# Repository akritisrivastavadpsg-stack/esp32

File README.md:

# esp32 Introduction

##
A basic ESP32 hardware project designed using KiCad. This repository contains the schematic and PCB layout files for an ESP32-based setup, intended for learning, experimentation, and future expansion.

📌 Project Overview

This project focuses on:

Understanding ESP32 pin mapping

Creating a clean schematic

Designing a basic PCB layout in KiCad

Laying groundwork for firmware-based ESP32 projects

No unnecessary complexity. Just the essentials done right.

🛠 Tools & Software

KiCad (v6 or later recommended)

ESP32 module (e.g., ESP32-WROOM-32)

Basic understanding of schematics & PCB design

/kicad/ 
├── schematic.sch 
├── pcb_layout.kicad_pcb 
└── project.kicad_pro

🔌 Hardware Features

ESP32 microcontroller

Power input section

Basic pin breakout for GPIO access

Designed for easy modification and upgrades

🚀 How to Use

Clone the repository:

git clone https://github.com/akritisrivastava20/esp32.git

Open the project in KiCad

Review the schematic

Inspect or modify the PCB layout

Export Gerber files if you plan to manufacture

⚠️ Notes

This is a basic-level project

Not optimized for production use

Always double-check power and pin connections before fabrication

📈 Future Improvements

Add USB-to-UART circuit

Voltage regulation improvements

On-board sensors or peripherals

Firmware examples (Arduino / ESP-IDF)

📜 License

This project is open-source. Use it, modify it, break it, learn from it.

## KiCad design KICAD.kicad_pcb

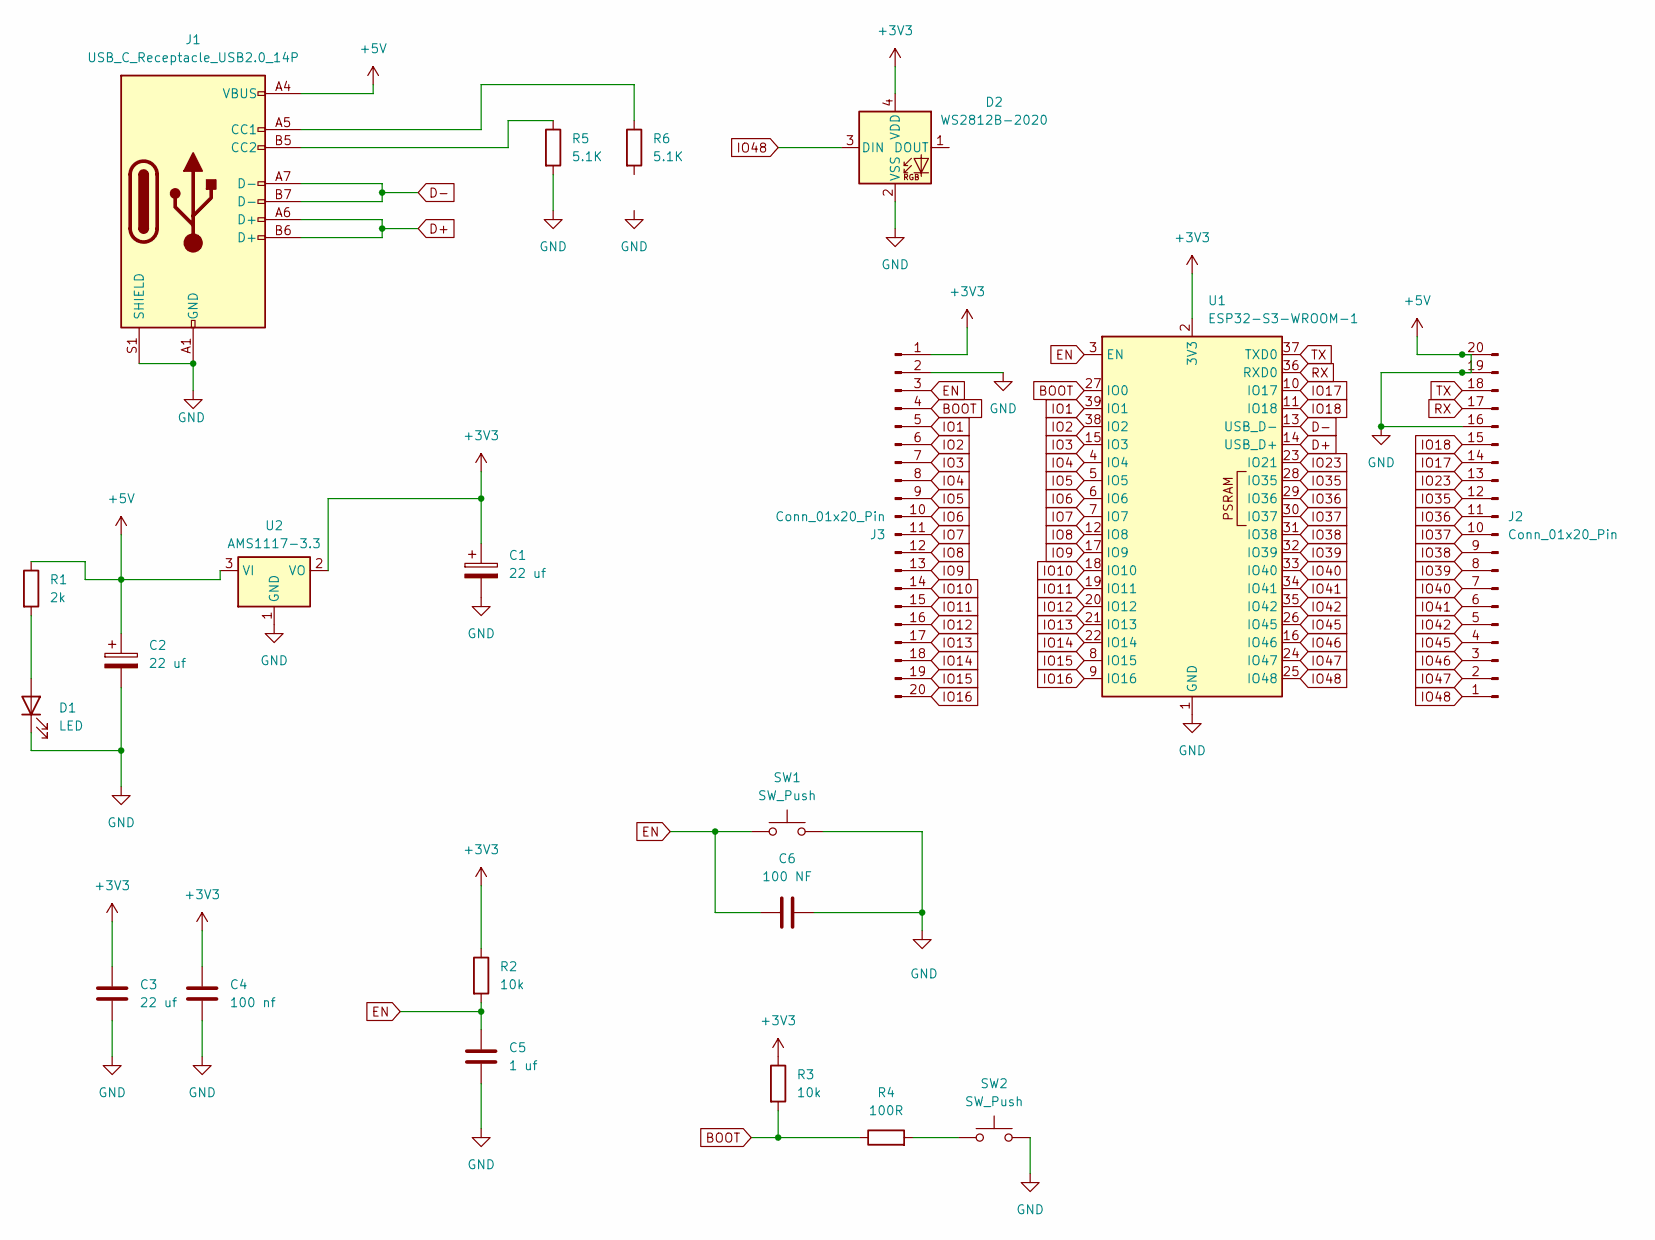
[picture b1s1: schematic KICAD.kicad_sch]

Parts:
C1, C2: 22 uf; CP_EIA-3528-12_Kemet-T
C3: 22 uf; C_0805_2012Metric
C4: 100 nf; C_0805_2012Metric
C5: 1 uf; C_0805_2012Metric
C6: 100 NF; C_0805_2012Metric
D1: LED; LED_0805_2012Metric
D2: WS2812B-2020; LED_WS2812B-2020_PLCC4_2.0x2.0mm
J1: USB_C_Receptacle_USB2.0_14P; USB_C_Receptacle_GCT_USB4105-xx-A_16P_TopMnt_Horizontal
J2, J3: Conn_01x20_Pin; PinHeader_1x20_P2.54mm_Vertical
R1: 2k; R_0805_2012Metric
R2, R3: 10k; R_0805_2012Metric
R4: 100R; R_0805_2012Metric
R5, R6: 5.1K; R_0805_2012Metric
SW1, SW2: SW_Push; SW_Push_SPST_NO_Alps_SKRK
U1: ESP32-S3-WROOM-1
U2: AMS1117-3.3; SOT-223-3_TabPin2

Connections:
+3V3: C1.1, C3.1, C4.1, D2.4 (VDD), J3.1, R2.1, R3.1, U1.2 (3V3), U2.2 (VO)
+5V: C1.2, C2.1, C2.2, C3.2, C4.2, C5.2, C6.2, D1.1 (K), D2.2 (VSS), J1.A1 (GND), J1.A4 (VBUS), J1.A9 (VBUS), J1.A12 (GND), J1.B1 (GND), J1.B4 (VBUS), J1.B9 (VBUS), J1.B12 (GND), J1.S1 (SHIELD), J2.16, J2.19, J2.20, J3.2, R1.1, R5.2, SW1.2, SW2.2, U1.1 (GND), U1.40 (GND), U1.41 (GND), U2.1 (GND), U2.3 (VI)
BOOT: J3.4, R3.2, R4.1, U1.27 (IO0)
D+: J1.A6 (D+), J1.B6 (D+), U1.14 (USB_D+)
D-: J1.A7 (D-), J1.B7 (D-), U1.13 (USB_D-)
EN: C5.1, C6.1, J3.3, R2.2, SW1.1, U1.3 (EN)
IO1: J3.5, U1.39 (IO1)
IO2: J3.6, U1.38 (IO2)
IO3: J3.7, U1.15 (IO3)
IO4: J3.8, U1.4 (IO4)
IO5: J3.9, U1.5 (IO5)
IO6: J3.10, U1.6 (IO6)
IO7: J3.11, U1.7 (IO7)
IO8: J3.12, U1.12 (IO8)
IO9: J3.13, U1.17 (IO9)
IO10: J3.14, U1.18 (IO10)
IO11: J3.15, U1.19 (IO11)
IO12: J3.16, U1.20 (IO12)
IO13: J3.17, U1.21 (IO13)
IO14: J3.18, U1.22 (IO14)
IO15: J3.19, U1.8 (IO15)
IO16: J3.20, U1.9 (IO16)
IO17: J2.14, U1.10 (IO17)
IO18: J2.15, U1.11 (IO18)
IO23: J2.13, U1.23 (IO21)
IO35: J2.12, U1.28 (IO35)
IO36: J2.11, U1.29 (IO36)
IO37: J2.10, U1.30 (IO37)
IO38: J2.9, U1.31 (IO38)
IO39: J2.8, U1.32 (IO39)
IO40: J2.7, U1.33 (IO40)
IO41: J2.6, U1.34 (IO41)
IO42: J2.5, U1.35 (IO42)
IO45: J2.4, U1.26 (IO45)
IO46: J2.3, U1.16 (IO46)
IO47: J2.2, U1.24 (IO47)
IO48: D2.3 (DIN), J2.1, U1.25 (IO48)
unnamed: D1.2 (A), R1.2
unnamed: J1.A5 (CC1), R6.1
unnamed: J1.B5 (CC2), R5.1
unnamed: R4.2, SW2.1
RX: J2.17, U1.36 (RXD0)
TX: J2.18, U1.37 (TXD0)

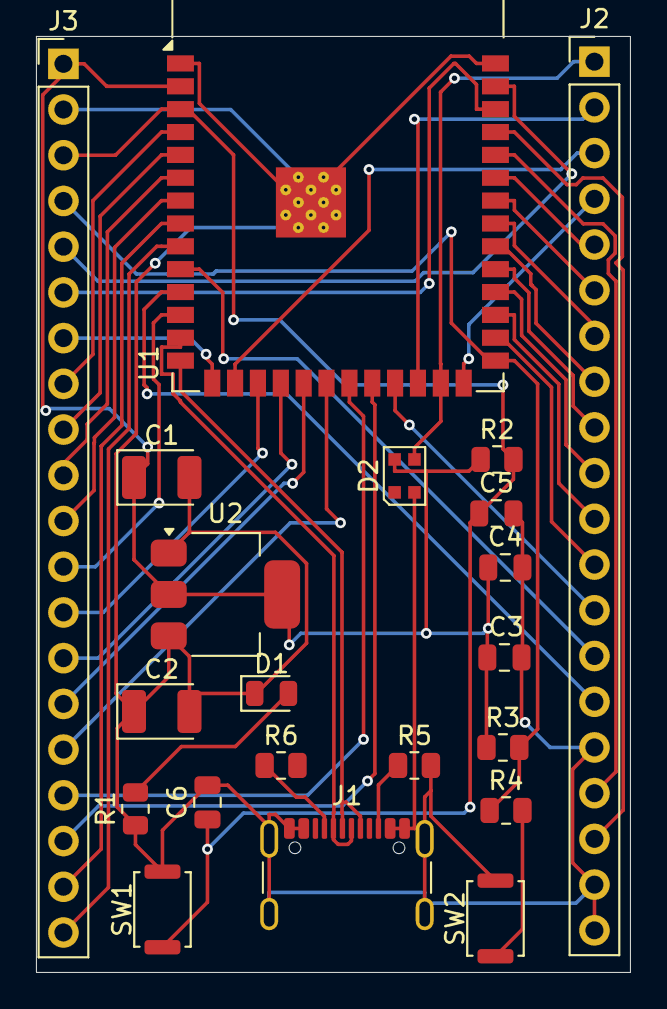
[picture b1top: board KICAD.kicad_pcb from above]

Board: 2 copper layers, 33.0 x 52.0 mm, 21 parts (0 on the bottom side), 43 nets.
